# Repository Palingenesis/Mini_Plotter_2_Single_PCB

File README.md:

# This is My Mini Plotter 2 with a Single PCB  
  
## This is a Board to control two basic bipolar stepper motors.  
  
## *The Board fitted to the Mini Plotter.*  
### Files for [KiCAD EDA](https://www.kicad.org/)  
There is [<span style="font-size: large;">**"Mini Plotter 2 Full.kicad_pcb.zip"**</span>](bom/) file  
* This can be used when **"Plot Files"** asked for at 
<sub></sub> 
when ordering 10 PCBs for $5  
* If you have <span style="font-size: large;">**[KiCAD EDA](https://www.kicad.org/)**</span>,  
<sub></sub>
have a Plugin  that will make things simple to order a PCB,  
just load this project into <span style="font-size: large;">**[KiCAD EDA](https://www.kicad.org/)**</span> install the plugin click the Icon  and it will create all the nesesery files needed and take you to order a PCB 
and compeate the form on 
<sub></sub> 
web site.  

### Files for [3D Printing](https://www.pcbway.com/rapid-prototyping/manufacture/?type=2&reffercode=TOP)  
There is [a folder with all the STL files needed](STL/) to print the Mini Plotter.

## Note!
The BOM only contains the Components for the Board.  
Other Parts required are:  
* Arduino Nano Module.
* 2 Stepper Motor 15mm dia. x 50mm Screw. (The type from CD or DVD drive)
* SG90 Servo.
* 3 lengths of 3mm Linear Rod.
* A light Spring 3mm x 25mm.
* 11 M1.7 x 6mm self tap flat nose screws.
* The 3D printed parts.
## About  
This is a PCBWay PCB Version of mini plotter I did quit a while ago, my original mini plotter I made of standard modules I bought and a home made PCB.

Details of the original can be found at my Blog here: [Tim's Mini Plotter 2 (tims-mini-plotter2.blogspot.com)](https://tims-mini-plotter2.blogspot.com/2019/01/tims-mini-plotter-2-this-is-new-project.html)

So it is the PCBWay PCB version.  
PCBWay do a great offer in prototyping PCBs, so I decided to make a version based around a single PCB.  
This is the same as the original except for the electronics, it has been made slightly longer to accommodate a single PCB.
## My Brief
For this project, I wanted to make a compact portable plotter using 2 motors from CD/DVD Drives.  
I wanted to use the cheap L298 drivers.  
I wanted to give it some memory where it can store some plots, and have a menu system to set some basic settings and be able to chose plots stored in memory.
## What I use
I use [FreeCAD](https://www.freecad.org/)  to design my 3D Prints, and [KiCAD EDA](https://www.kicad.org/) to design my PCB.  
Both these programs can integrate with each other. They are open source and I recommend them.  
[KiCAD EDA](https://www.kicad.org/) also has a plugin  from <sub></sub> that makes it simple to order PCBs.
## History
My previous Mini Plotter Ver. 1 looked like this: [Version 1](https://tims-mini-plotter-1.blogspot.com/) [Version 1.3](https://www.youtube.com/watch?v=I_yTPbJcGrc&feature=youtu.be)
### Here is is a video of the original Mini Plotter 2 to show how it works.
*Click this image to see a video of it in use.*

This new version works exactly in the same way.
## Stepper Motors
  
The stepper motors I am using for this project are motors I repurposed from some CD/DVD drives.  
The dimensions are approximate, I have put holes to suit what I have shown.  
Care should be taken when soldering new cables to these motors, it is very easy to melt the coil bobbins.  
The only data I could find for these type of motors was from a data sheet for a PL15S-020. (I will assume other makes are similar)  
  
If we do a little maths: V=ri, 5 volt divided by 10 ohms = 0.5 Amps  
As I could check the resistance of my motors and found them to have 12 ohm resistance.  
I will work on the assumption mine require 0.4A. (5/12=0.42A)  
They probably are designed to take 0.5A, but: they are normally mounted to a large metal frame that acts like a massive heat sink.  
My steppers are going to be mounted to plastic. (PLA)  
Knowing this I will be wiring the Voltage regulators in the Constant Current configuration. (see L78xx family data sheets)  
I had some 12.5 ohm 2 Watt Resistors, so I have 2 for each drive.  
12.5 ohm 2 Watt two in parallel making 6.25 ohm.  
## Motor Driver
I have used two L293 drivers to drive the stepper motors.  
  
## Memory
I have used two 24C256 I2C Memory Chips, there is room for three.  
  
To program the memory you will need the Application I wrote and some Arduino code.  
I have gone into detail of how I compress G-Code command lines to 3 bytes on my blog here: [Adding Memory to Arduino NANO and compressing G-Code (tims-mini-plotter2.blogspot.com)](https://tims-mini-plotter2.blogspot.com/2019/04/adding-memory-to-arduino-nano-and.html)  
## Servo
The servo is any SG90.  
  
The horn I used had two long and two short arms.  
## Display
The display is an I2C 0.9 inch OLED  
  
## Power
I have added the L7805 to power the servo or a laser.  
Any 5v auxiliary device can be attached to this switched output.  
The Arduino Nano has its own Linear regulator, this regulator limits the input voltage to 12v. (I should have wired it differently)  
The plotter runs best above 10 Volts.  
## Assembly Of the Plotter.
Assembly is the same as I did with the original here: [Tim's Mini Plotter 2: Assembly (tims-mini-plotter2.blogspot.com)](https://tims-mini-plotter2.blogspot.com/2019/03/assembly.html)  
The only difference is the parts use.  
* There is a [folder of Images ](Assembly_Images/) that show how these parts go to gether.  
* As I mentioned, this is modified to take the new Single PCB by <sub></sub>.  
* Please read some of the original Blog, There are things that need attention. The Screw Pad, The Linear Rod Fit.  
## Instructable.  
I have also done an Instructable of the new version.  
[Tim's Mini Plotter 2 With Single PCB](https://www.instructables.com/Tims-Mini-Plotter-2-With-Single-PCB/)  
## I did some Live Streams should you want to make this.
These are the sort of stream you click through to find the info you want.  
Treat them like a reference book. :)    
[Tim Live Part 1 of Mini Plotter (youtube.com)](https://www.youtube.com/watch?v=YSE00Mr2BqY)  
[Tim Live Part 2 of Mini Plotter (youtube.com)](https://www.youtube.com/watch?v=kGypXZ9P3tI&t=1s)  
[Tim Live Part 3 of Mini Plotter (youtube.com)](https://www.youtube.com/watch?v=wI7Unksa26g&t=3s)

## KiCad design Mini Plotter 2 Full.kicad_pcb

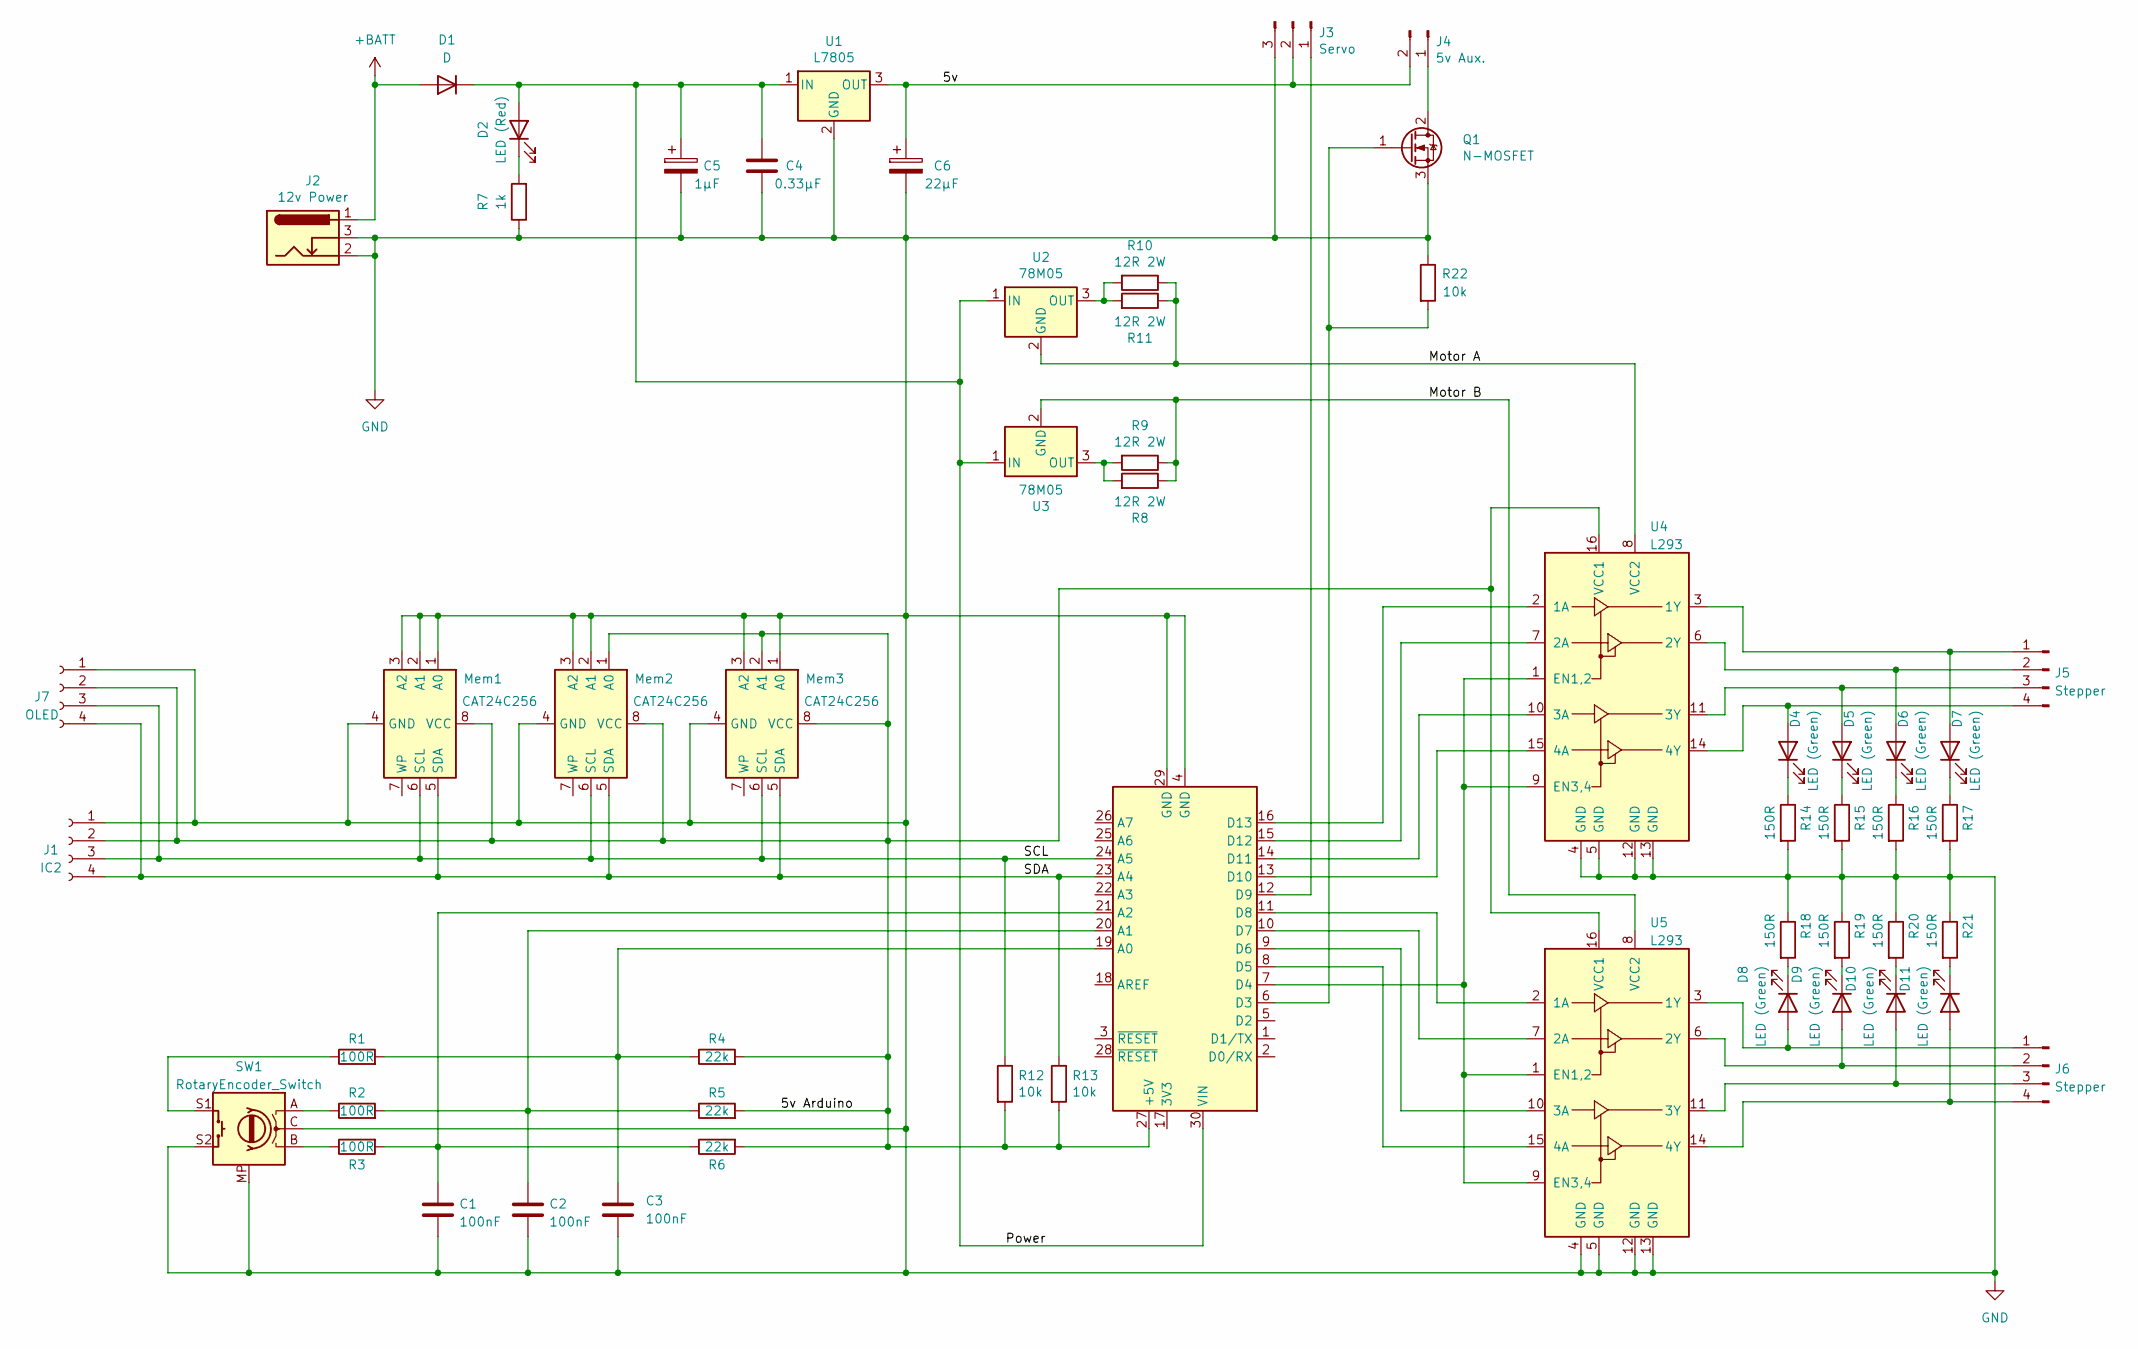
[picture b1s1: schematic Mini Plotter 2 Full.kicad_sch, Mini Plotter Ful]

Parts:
A1: Arduino_Nano_v3.x; Arduino_Nano_WithMountingHoles
C1, C2, C3: 100nF; C_0805_2012Metric
C4: 0.33µF; C_0805_2012Metric
C5: 1µF; CP_Radial_D4.0mm_P2.00mm
C6: 22µF; CP_Radial_D4.0mm_P2.00mm
D1: D; D_SMA-SMB_Universal_Handsoldering
D2: LED (Red); LED_0805_2012Metric
D4, D5, D6, D7, D8, D9, D10, D11: LED (Green); LED_0805_2012Metric
J1: IC2; PinSocket_1x04_P2.54mm_Vertical
J2: 12v Power; BarrelJack_Horizontal
J3: Servo; PinHeader_1x03_P2.54mm_Vertical
J4: 5v Aux.; PinHeader_1x02_P2.54mm_Vertical
J5, J6: Stepper; PinHeader_1x04_P2.54mm_Vertical
J7: OLED; OLED_I2C_096in_Module
Mem1, Mem2, Mem3: CAT24C256; DIP-8_W7.62mm_Socket
Q1: N-MOSFET; TO-252-3_TabPin2
R1, R2, R3: 100R; R_0805_2012Metric
R4, R5, R6: 22k; R_0805_2012Metric
R7: 1k; R_0805_2012Metric
R8, R9, R10, R11: 12R 2W; R_Axial_DIN0516_L15.5mm_D5.0mm_P20.32mm_Horizontal
R12, R13, R22: 10k; R_0805_2012Metric
R14, R15, R16, R17, R18, R19, R20, R21: 150R; R_0805_2012Metric
SW1: RotaryEncoder_Switch; RotaryEncoder_Alps_EC11E-Switch_Vertical_H20mm
U1: L7805; TO-252-2
U2, U3: 78M05; TO-252-2
U4, U5: L293; DIP-16_W7.62mm_Socket

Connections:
+BATT: D1.2 (A), J2.1
/5v: C6.1, J3.2, J4.2, U1.3 (OUT)
/5v Arduino: A1.27 (+5V), J1.2, J7.2, Mem1.8 (VCC), Mem2.1 (A0), Mem2.8 (VCC), Mem3.2 (A1), Mem3.8 (VCC), R4.2, R5.2, R6.2, R12.2, R13.2, U4.16 (VCC1), U5.16 (VCC1)
/Motor A: R10.1, R11.1, U2.2 (GND), U4.8 (VCC2)
/Motor B: R8.1, R9.1, U3.2 (GND), U5.8 (VCC2)
/Power: A1.30 (VIN), C4.1, C5.1, D1.1 (K), D2.2 (A), U1.1 (IN), U2.1 (IN), U3.1 (IN)
/SCL: A1.24 (A5), J1.3, J7.3, Mem1.6 (SCL), Mem2.6 (SCL), Mem3.6 (SCL), R12.1
/SDA: A1.23 (A4), J1.4, J7.4, Mem1.5 (SDA), Mem2.5 (SDA), Mem3.5 (SDA), R13.1
GND: A1.4 (GND), A1.29 (GND), C1.2, C2.2, C3.2, C4.2, C5.2, C6.2, J1.1, J2.2, J2.3, J3.3, J7.1, Mem1.1 (A0), Mem1.2 (A1), Mem1.3 (A2), Mem1.4 (GND), Mem2.2 (A1), Mem2.3 (A2), Mem2.4 (GND), Mem3.1 (A0), Mem3.3 (A2), Mem3.4 (GND), Q1.3 (S), R7.1, R14.2, R15.2, R16.2, R17.2, R18.1, R19.1, R20.1, R21.1, R22.1, SW1.C, SW1.MP (Case), SW1.S2, U1.2 (GND), U4.4 (GND), U4.5 (GND), U4.12 (GND), U4.13 (GND), U5.4 (GND), U5.5 (GND), U5.12 (GND), U5.13 (GND)
unnamed: A1.19 (A0), C3.1, R1.2, R4.1
unnamed: A1.20 (A1), C2.1, R2.2, R5.1
unnamed: A1.21 (A2), C1.1, R3.2, R6.1
unnamed: A1.6 (D3), Q1.1 (G), R22.2
unnamed: A1.7 (D4), U4.1 (EN1,2), U4.9 (EN3,4), U5.1 (EN1,2), U5.9 (EN3,4)
unnamed: A1.8 (D5), U5.15 (4A)
unnamed: A1.9 (D6), U5.10 (3A)
unnamed: A1.10 (D7), U5.7 (2A)
unnamed: A1.11 (D8), U5.2 (1A)
unnamed: A1.12 (D9), J3.1
unnamed: A1.13 (D10), U4.15 (4A)
unnamed: A1.14 (D11), U4.10 (3A)
unnamed: A1.15 (D12), U4.7 (2A)
unnamed: A1.16 (D13), U4.2 (1A)
unnamed: D2.1 (K), R7.2
unnamed: D4.2 (A), J5.4, U4.14 (4Y)
unnamed: D4.1 (K), R14.1
unnamed: D5.2 (A), J5.3, U4.11 (3Y)
unnamed: D5.1 (K), R15.1
unnamed: D6.2 (A), J5.2, U4.6 (2Y)
unnamed: D6.1 (K), R16.1
unnamed: D7.2 (A), J5.1, U4.3 (1Y)
unnamed: D7.1 (K), R17.1
unnamed: D8.2 (A), J6.1, U5.3 (1Y)
unnamed: D8.1 (K), R18.2
unnamed: D9.2 (A), J6.2, U5.6 (2Y)
unnamed: D9.1 (K), R19.2
unnamed: D10.2 (A), J6.3, U5.11 (3Y)
unnamed: D10.1 (K), R20.2
unnamed: D11.2 (A), J6.4, U5.14 (4Y)
unnamed: D11.1 (K), R21.2
unnamed: J4.1, Q1.2 (D)
unnamed: R1.1, SW1.S1
unnamed: R2.1, SW1.A
unnamed: R3.1, SW1.B
unnamed: R10.2, R11.2, U2.3 (OUT)
unnamed: R8.2, R9.2, U3.3 (OUT)

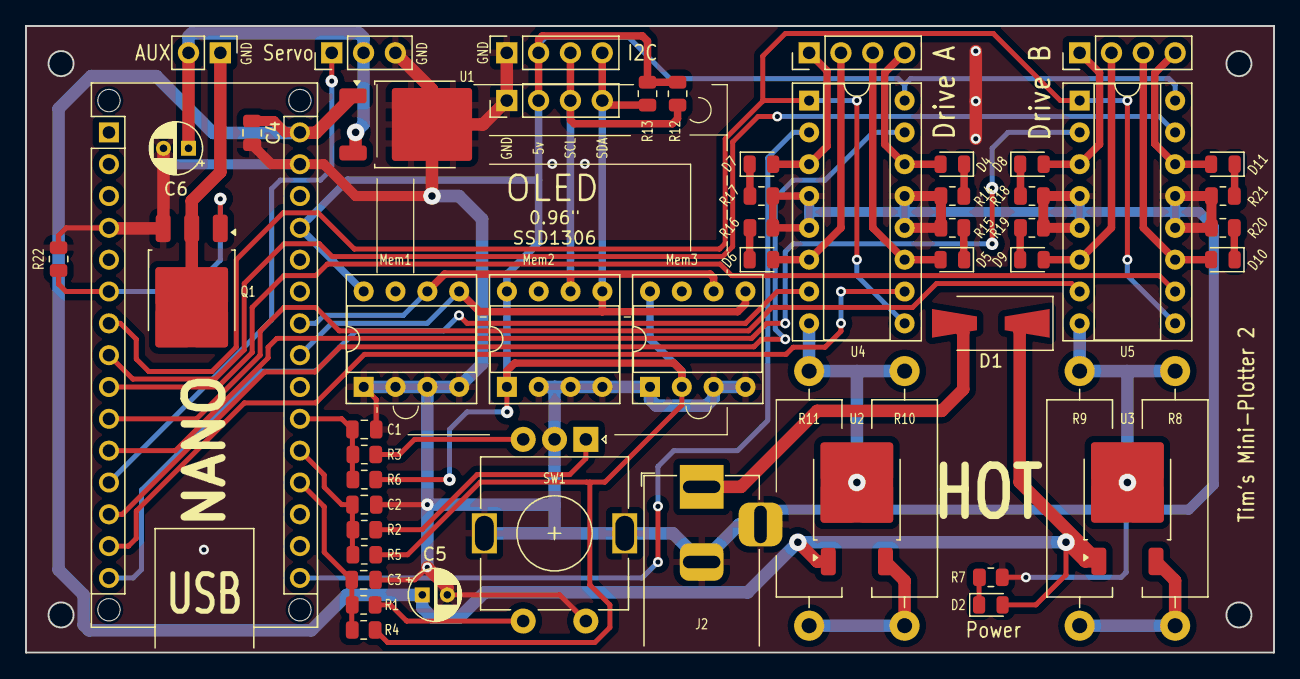
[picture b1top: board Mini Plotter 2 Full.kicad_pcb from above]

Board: 2 copper layers, 99.6 x 50.0 mm, 56 parts (0 on the bottom side), 46 nets.

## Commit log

2024-08-06 Initial Publish
2024-08-06 Add STL Files
2024-08-06 Added Image
2024-08-06 Edit MD
2024-11-18 Update README.md
    added Instructable link
2024-11-18 Update README.md
    Edit Text
2024-11-18 Update README.md
    edit
2024-11-27 Updated EEPROM_Writer.zip
2025-02-20 Added FreeCAD Files
2025-03-22 Added AVRDUDE
2025-03-24 changed avrdude zip
